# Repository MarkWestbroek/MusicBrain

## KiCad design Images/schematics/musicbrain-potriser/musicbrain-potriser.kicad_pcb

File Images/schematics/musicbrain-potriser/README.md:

# MusicBrain POT-RISER — MCP3208-riser voor het POT8-FRONT

**Status**: ERC 0, netlijst pad-voor-pad geverifieerd, DRC 0/0. Bord 28×80 mm, 2 lagen.
**Model**: route 2 — het domme POT8-FRONT ligt plat aan het paneel; deze smalle
riser staat eronder in het busboard-slot en draagt de elektronica.

## Connectoren

- **J1** (haakse male 2×10, onderrand): het busboard-slot in. Gebruikt alleen
  GND / +3V3 / SCLK / MOSI / MISO / CS; de rest (±12V, LDAC, IRQ, I2C, SPARE)
  is onaangesloten.
- **J2** (haakse male 1×10, bovenrand): het POT8-FRONT in.
  **Contract: 1 = GND, 2..9 = W1..W8 (lopers), 10 = +3V3.**
  ⚠️ Pin-1-oriëntatie t.o.v. de front-socket bij de eerste passing verifiëren
  (front-socket zit op de achterzijde); klopt de volgorde niet, dan de
  J2-map in `gen_potriser.py` spiegelen en regenereren.

## Elektrisch

- MCP3208 (SOIC-16), SPI mode 0, ratiometrisch (VREF = VDD = +3V3).
- CH0..CH7 = W1..W8 = paneel boven→onder.
- 100 nF-laadreservoir per loper (C1–C8) direct achter J2, 100 nF ontkoppeling (C9).
- Firmware: bestaande `MbPot8`-driver werkt ongewijzigd (zelfde chip + mapping).

## Waarom dit bord

De pot8-slotkaart (110×80, met haakse pots erop) is geen drager voor het
front-model: pots zitten in de weg, geen frontconnector en onnodig breed
(besluit 2026-07-11). Deze riser vervangt hem in het pot-spoor; de pot8-kaart
blijft bruikbaar als losstaand alternatief zonder front.

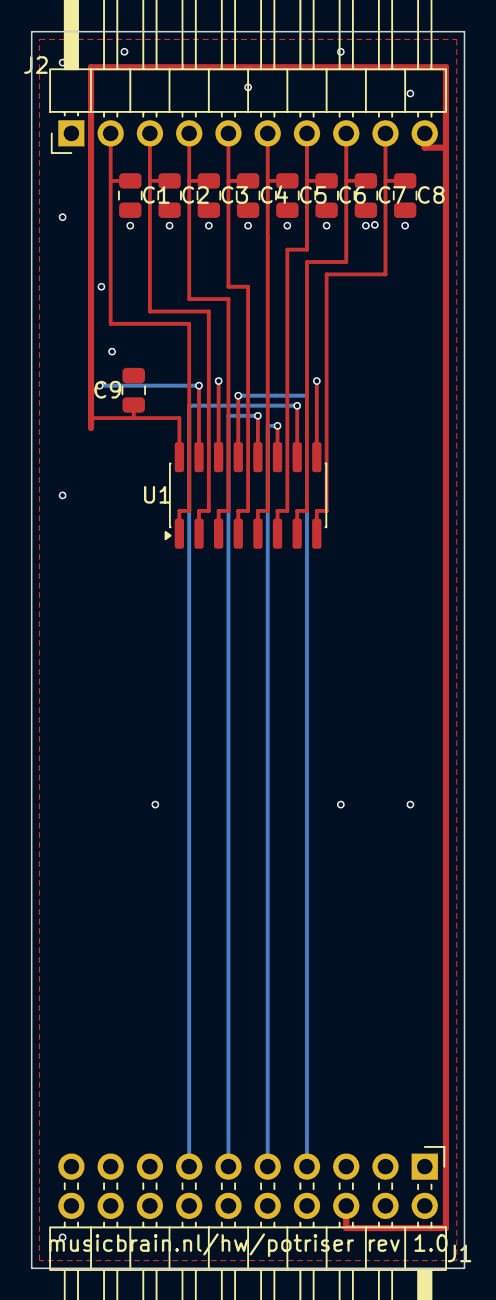
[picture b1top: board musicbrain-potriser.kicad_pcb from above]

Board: 2 copper layers, 28.0 x 80.0 mm, 12 parts (0 on the bottom side), 14 nets.

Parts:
C1, C2, C3, C4, C5, C6, C7, C8, C9: 100n; C_0805_2012Metric
J1: BUS; PinHeader_2x10_P2.54mm_Horizontal
J2: NAAR FRONT; PinHeader_1x10_P2.54mm_Horizontal
U1: MCP3208; SOIC-16_3.9x9.9mm_P1.27mm

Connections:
+3V3: C9.1, J1.6, J2.10, U1.15, U1.16
/CS: J1.13, U1.10
/MISO: J1.11, U1.12
/MOSI: J1.9, U1.11
/SCLK: J1.7, U1.13
/W1: C1.1, J2.2, U1.1
/W2: C2.1, J2.3, U1.2
/W3: C3.1, J2.4, U1.3
/W4: C4.1, J2.5, U1.4
/W5: C5.1, J2.6, U1.5
/W6: C6.1, J2.7, U1.6
/W7: C7.1, J2.8, U1.7
/W8: C8.1, J2.9, U1.8
GND: C1.2, C2.2, C3.2, C4.2, C5.2, C6.2, C7.2, C8.2, C9.2, J1.1, J1.3, J1.5, J1.8, J1.10, J1.12, J1.14, J2.1, U1.9, U1.14

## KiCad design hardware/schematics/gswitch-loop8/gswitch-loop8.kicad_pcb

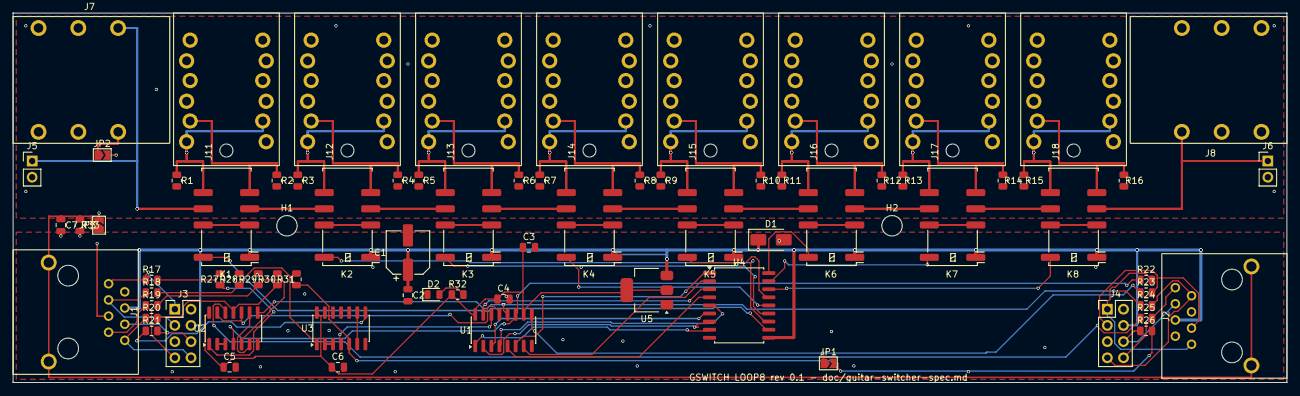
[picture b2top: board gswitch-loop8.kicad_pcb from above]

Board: 2 copper layers, 200.0 x 58.0 mm, 76 parts (0 on the bottom side), 82 nets.

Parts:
C1: 100u/25V; CP_Elec_6.3x7.7
C2, C4, C5, C6, C7: 100n; C_0805_2012Metric
C3: 10u; C_0805_2012Metric
D1: SMAJ15A; D_SMA
D2: LED-GN; LED_0805_2012Metric
H1, H2: M3; MH32
J1, J2: RJ45-S; RJ45_shielded
J3: CHAIN-LINK-IN; PinHeader_2x04_P2.54mm_Vertical
J4: CHAIN-LINK-UIT; PinHeader_2x04_P2.54mm_Vertical
J5: AUDIO-LINK-IN; PinHeader_1x02_P2.54mm_Vertical
J6: AUDIO-LINK-UIT; PinHeader_1x02_P2.54mm_Vertical
J7, J8: ACJS-MH; ACJS_MH
J11, J12, J13, J14, J15, J16, J17, J18: ACJS-MHD; ACJS_MHD
JP1: TERM; SolderJumper-2_P1.3mm_Open_TrianglePad1.0x1.5mm
JP2: IN-TN=AGND; SolderJumper-2_P1.3mm_Open_TrianglePad1.0x1.5mm
JP3: AGND=CHASSIS; SolderJumper-2_P1.3mm_Open_TrianglePad1.0x1.5mm
K1, K2, K3, K4, K5, K6, K7, K8: EE2-12NU/TQ2SA-12V; Relay_DPDT_Kemet_EE2_NU
R1, R2, R3, R4, R5, R6, R7, R8, R9, R10, R11, R12, R13, R14, R15, R16, R33: 1M; R_0805_2012Metric
R17, R18, R19, R20, R21, R22, R23, R24, R25, R26: 100R; R_0805_2012Metric
R27, R28, R29, R30, R31: 100k; R_0805_2012Metric
R32: 4k7; R_0805_2012Metric
U1: 74HC595; SOIC-16_3.9x9.9mm_P1.27mm
U2, U3: 74HC14; SOIC-14_3.9x8.7mm_P1.27mm
U4: ULN2803A; SOIC-18W_7.5x11.6mm_P1.27mm
U5: AMS1117-5.0; SOT-223-3_TabPin2

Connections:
+5V: C3.1, C4.1, C5.1, C6.1, R32.1, U1.10, U1.16, U2.14, U3.14, U5.2
+12V: C1.1, C2.1, D1.1, J1.4, J2.4, J3.4, J4.4, K1.1, K2.1, K3.1, K4.1, K5.1, K6.1, K7.1, K8.1, U4.10, U5.3
/AGND: J5.2, J6.2, J7.R, J7.RN, J7.S, J7.SN, J8.R, J8.RN, J8.S, J8.SN, J11.1, J11.2, J11.4, J11.5, J11.7, J11.8, J11.10, J11.11, J12.1, J12.2, J12.4, J12.5, J12.7, J12.8, J12.10, J12.11, J13.1, J13.2, J13.4, J13.5, J13.7, J13.8, J13.10, J13.11, J14.1, J14.2, J14.4, J14.5, J14.7, J14.8, J14.10, J14.11, J15.1, J15.2, J15.4, J15.5, J15.7, J15.8, J15.10, J15.11, J16.1, J16.2, J16.4, J16.5, J16.7, J16.8, J16.10, J16.11, J17.1, J17.2, J17.4, J17.5, J17.7, J17.8, J17.10, J17.11, J18.1, J18.2, J18.4, J18.5, J18.7, J18.8, J18.10, J18.11, JP2.2, JP3.2, R1.2, R2.2, R3.2, R4.2, R5.2, R6.2, R7.2, R8.2, R9.2, R10.2, R11.2, R12.2, R13.2, R14.2, R15.2, R16.2
/BYP1: K1.3, K1.10
/BYP2: K2.3, K2.10
/BYP3: K3.3, K3.10
/BYP4: K4.3, K4.10
/BYP5: K5.3, K5.10
/BYP6: K6.3, K6.10
/BYP7: K7.3, K7.10
/BYP8: K8.3, K8.10
/CHASSIS: C7.1, J1.SH, J2.SH, JP3.1, R33.1
/CLK_A: R17.2, R27.1, U2.1
/CLK_J: J1.1, J3.1, R17.1
/CLK_N: U2.2, U2.3
/CLK_O: R22.1, U1.11, U2.4
/CLK_T: J2.1, J4.1, R22.2
/D1: U1.1, U4.8
/D2: U1.2, U4.7
/D3: U1.3, U4.6
/D4: U1.4, U4.5
/D5: U1.5, U4.4
/D6: U1.6, U4.1
/D7: U1.7, U4.2
/D8: U1.15, U4.3
/DATA_A: R18.2, R28.1, U3.1
/DATA_J: J1.3, J3.3, R18.1
/DATA_N: U3.2, U3.3
/DATA_O: U1.14, U3.4
/DRETT_J: J2.6, J4.6, R26.1
/DRET_A: JP1.2, R26.2, R31.1, U3.5
/DRET_J: J1.6, J3.6, R21.2
/DRET_N: U3.6, U3.9
/DRET_O: R21.1, U3.8
/EN_A: R20.2, R30.1, U2.11
/EN_J: J1.8, J3.8, R20.1
/EN_O: R25.1, U2.12
/EN_T: J2.8, J4.8, R25.2
/INTN: J7.TN, JP2.1
/LATCH_A: R19.2, R29.1, U2.5
/LATCH_J: J1.7, J3.7, R19.1
/LATCH_N: U2.6, U2.9
/LATCH_O: R24.1, U1.12, U2.8
/LATCH_T: J2.7, J4.7, R24.2
/LEDA: D2.2, R32.2
/N0: J5.1, J7.T, K1.9
/N1: K1.4, K2.9
/N2: K2.4, K3.9
/N3: K3.4, K4.9
/N4: K4.4, K5.9
/N5: K5.4, K6.9
/N6: K6.4, K7.9
/N7: K7.4, K8.9
/N8: J6.1, J8.T, K8.4
/OE_N: U1.13, U2.10, U2.13
/RET1: J11.6, K1.5, R2.1
/RET2: J12.6, K2.5, R4.1
/RET3: J13.6, K3.5, R6.1
/RET4: J14.6, K4.5, R8.1
/RET5: J15.6, K5.5, R10.1
/RET6: J16.6, K6.5, R12.1
/RET7: J17.6, K7.5, R14.1
/RET8: J18.6, K8.5, R16.1
/RLY1: K1.12, U4.11
/RLY2: K2.12, U4.12
/RLY3: K3.12, U4.13
/RLY4: K4.12, U4.14
/RLY5: K5.12, U4.15
/RLY6: K6.12, U4.18
/RLY7: K7.12, U4.17
/RLY8: K8.12, U4.16
/SEND1: J11.3, J11.12, K1.8, R1.1
/SEND2: J12.3, J12.12, K2.8, R3.1
/SEND3: J13.3, J13.12, K3.8, R5.1
/SEND4: J14.3, J14.12, K4.8, R7.1
/SEND5: J15.3, J15.12, K5.8, R9.1
/SEND6: J16.3, J16.12, K6.8, R11.1
/SEND7: J17.3, J17.12, K7.8, R13.1
/SEND8: J18.3, J18.12, K8.8, R15.1
/SER: JP1.1, R23.1, U1.9
/SER_T: J2.3, J4.3, R23.2
GND: C1.2, C2.2, C3.2, C4.2, C5.2, C6.2, C7.2, D1.2, D2.1, J1.2, J1.5, J2.2, J2.5, J3.2, J3.5, J4.2, J4.5, R27.2, R28.2, R29.2, R30.2, R31.2, R33.2, U1.8, U2.7, U3.7, U3.11, U3.13, U4.9, U5.1

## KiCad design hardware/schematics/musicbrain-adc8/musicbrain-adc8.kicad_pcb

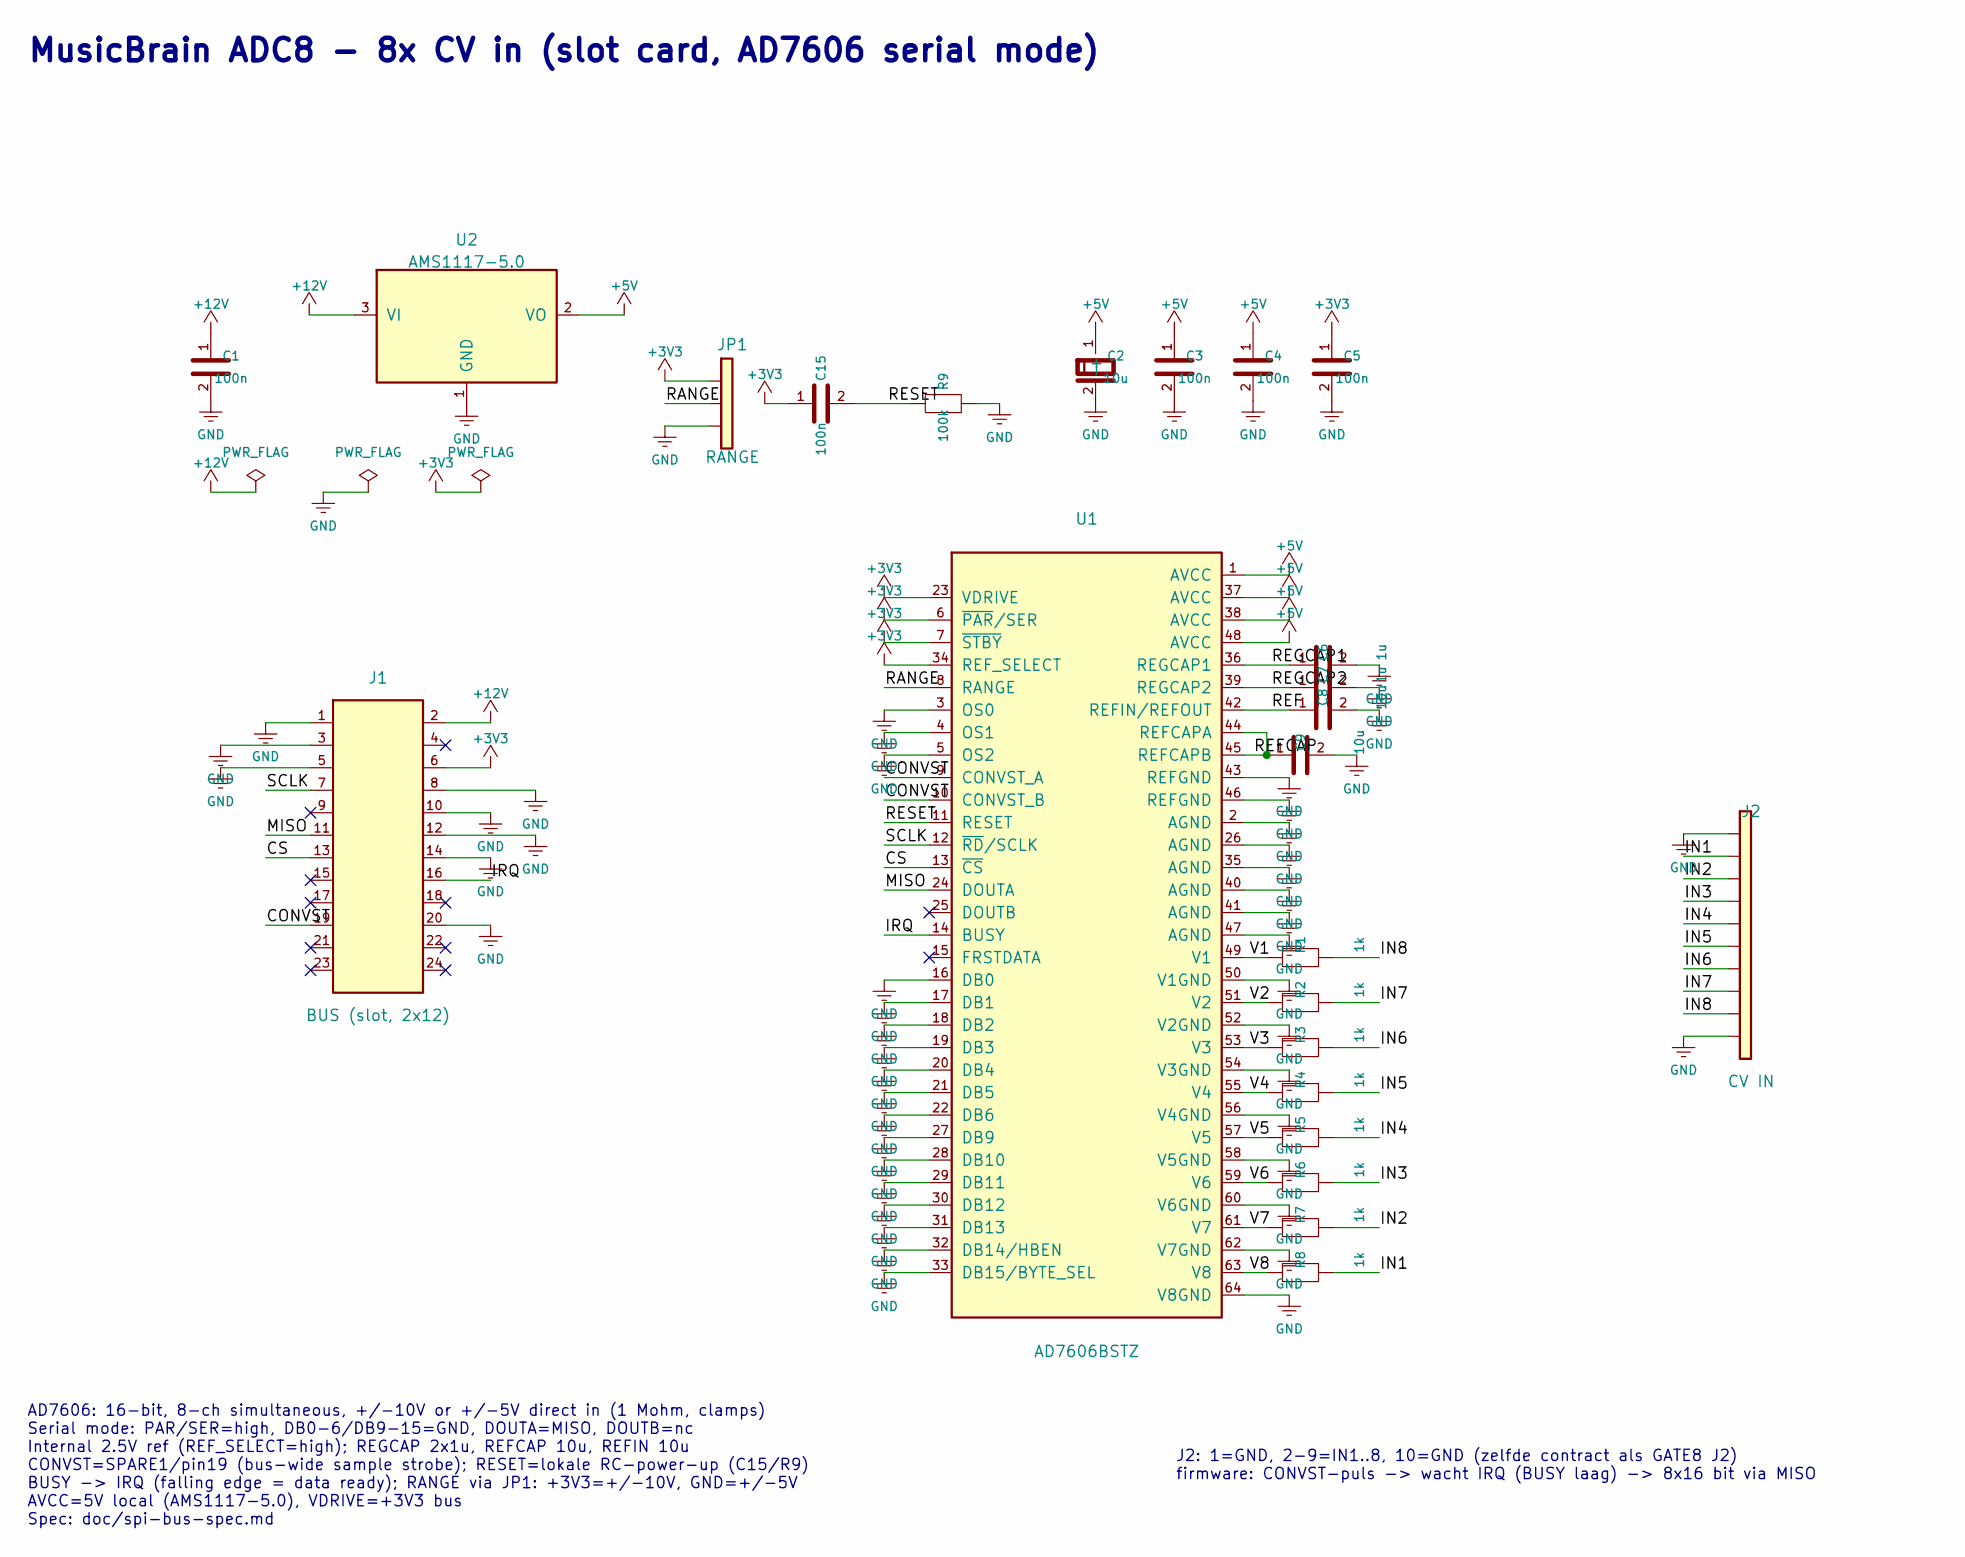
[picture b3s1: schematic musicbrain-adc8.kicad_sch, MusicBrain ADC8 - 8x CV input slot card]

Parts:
C1, C3, C4, C5, C15: 100n; C_0805_2012Metric
C2: 10u; CP_Elec_4x5.3
C6, C7: 1u; C_0805_2012Metric
C8, C9: 10u; C_0805_2012Metric
J1: BUS (slot, 2x12); PinHeader_2x12_P2.54mm_Horizontal
J2: CV IN; PinHeader_1x10_P2.54mm_Horizontal
JP1: RANGE; PinHeader_1x03_P2.54mm_Vertical
R1, R2, R3, R4, R5, R6, R7, R8: 1k; R_0805_2012Metric
R9: 100k; R_0805_2012Metric
U1: AD7606BSTZ; LQFP-64_10x10mm_P0.5mm
U2: AMS1117-5.0; SOT-223-3_TabPin2

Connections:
+3V3: C5.1, C15.1, J1.6, JP1.1, U1.6 (~PAR/SER), U1.7 (~STBY), U1.23 (VDRIVE), U1.34 (REF_SELECT)
+5V: C2.1 (+), C3.1, C4.1, U1.1 (AVCC), U1.37 (AVCC), U1.38 (AVCC), U1.48 (AVCC), U2.2 (VO)
+12V: C1.1, J1.2, U2.3 (VI)
/CONVST: J1.19, U1.9 (CONVST_A), U1.10 (CONVST_B)
/CS: J1.13, U1.13 (~CS)
/IN1: J2.2, R8.2
/IN2: J2.3, R7.2
/IN3: J2.4, R6.2
/IN4: J2.5, R5.2
/IN5: J2.6, R4.2
/IN6: J2.7, R3.2
/IN7: J2.8, R2.2
/IN8: J2.9, R1.2
/IRQ: J1.16, U1.14 (BUSY)
/MISO: J1.11, U1.24 (DOUTA)
/RANGE: JP1.2, U1.8 (RANGE)
/REF: C8.1, U1.42 (REFIN/REFOUT)
/REFCAP: C9.1, U1.44 (REFCAPA), U1.45 (REFCAPB)
/REGCAP1: C6.1, U1.36 (REGCAP1)
/REGCAP2: C7.1, U1.39 (REGCAP2)
/RESET: C15.2, R9.1, U1.11 (RESET)
/SCLK: J1.7, U1.12 (~RD/SCLK)
/V1: R1.1, U1.49 (V1)
/V2: R2.1, U1.51 (V2)
/V3: R3.1, U1.53 (V3)
/V4: R4.1, U1.55 (V4)
/V5: R5.1, U1.57 (V5)
/V6: R6.1, U1.59 (V6)
/V7: R7.1, U1.61 (V7)
/V8: R8.1, U1.63 (V8)
GND: C1.2, C2.2 (-), C3.2, C4.2, C5.2, C6.2, C7.2, C8.2, C9.2, J1.1, J1.3, J1.5, J1.8, J1.10, J1.12, J1.14, J1.20, J2.1, J2.10, JP1.3, R9.2, U1.2 (AGND), U1.3 (OS0), U1.4 (OS1), U1.5 (OS2), U1.16 (DB0), U1.17 (DB1), U1.18 (DB2), U1.19 (DB3), U1.20 (DB4), U1.21 (DB5), U1.22 (DB6), U1.26 (AGND), U1.27 (DB9), U1.28 (DB10), U1.29 (DB11), U1.30 (DB12), U1.31 (DB13), U1.32 (DB14/HBEN), U1.33 (DB15/BYTE_SEL), U1.35 (AGND), U1.40 (AGND), U1.41 (AGND), U1.43 (REFGND), U1.46 (REFGND), U1.47 (AGND), U1.50 (V1GND), U1.52 (V2GND), U1.54 (V3GND), U1.56 (V4GND), U1.58 (V5GND), U1.60 (V6GND), U1.62 (V7GND), U1.64 (V8GND), U2.1 (GND)

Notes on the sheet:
MusicBrain ADC8 - 8x CV in (slot card, AD7606 serial mode)
AD7606: 16-bit, 8-ch simultaneous, +/-10V or +/-5V direct in (1 Mohm, clamps) Serial mode: PAR/SER=high, DB0-6/DB9-15=GND, DOUTA=MISO, DOUTB=nc Internal 2.5V ref (REF_SELECT=high); REGCAP 2x1u, REFCAP 10u, REFIN 10u CONVST=SPARE1/pin19 (bus-wide sample strobe); RESET=lokale RC-power-up (C15/R9) BUS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
J2: 1=GND, 2-9=IN1..8, 10=GND (zelfde contract als GATE8 J2) firmware: CONVST-puls -> wacht IRQ (BUSY laag) -> 8x16 bit via MISO

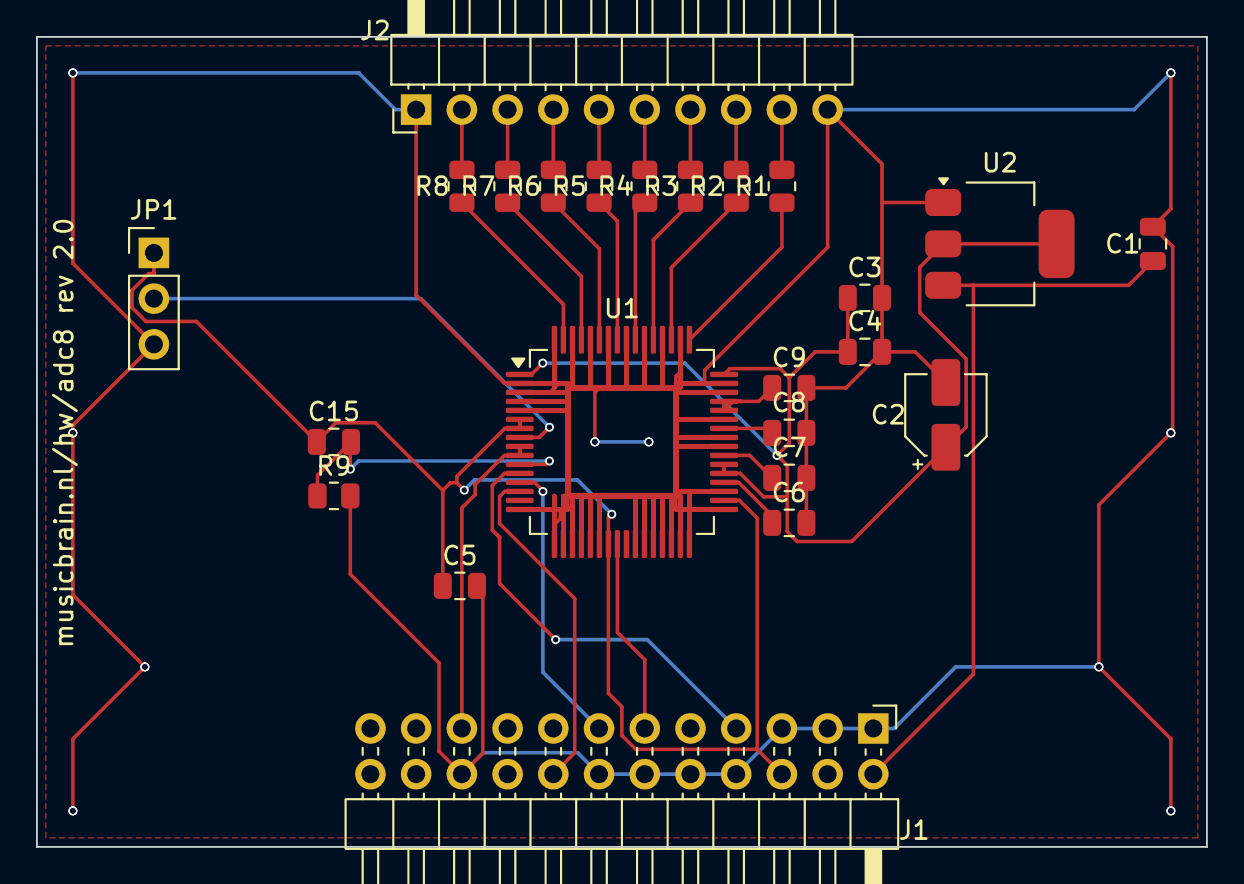
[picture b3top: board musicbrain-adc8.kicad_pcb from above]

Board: 2 copper layers, 65.0 x 45.0 mm, 24 parts (0 on the bottom side), 31 nets.

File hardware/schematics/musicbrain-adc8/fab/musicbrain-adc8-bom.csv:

"Comment","Designator","Footprint","LCSC Part #"
"100n","C1,C3,C4,C5","C_0805_2012Metric","C49678"
"10u","C2","CP_Elec_4x5.3","C3343"
"1u","C6,C7","C_0805_2012Metric","C5137478"
"10u","C8,C9","C_0805_2012Metric","C440198"
"BUS","J1","PinHeader_2x10_P2.54mm_Vertical",""
"CV IN","J2","PinHeader_1x10_P2.54mm_Vertical",""
"RANGE","JP1","PinHeader_1x03_P2.54mm_Vertical","C49257"
"1k","R1,R2,R3,R4,R5,R6,R7,R8","R_0805_2012Metric","C17513"
"100k","R9","R_0805_2012Metric","C149504"
"AD7606BSTZ","U1","LQFP-64_10x10mm_P0.5mm","C398827"
"AMS1117-5.0","U2","SOT-223-3_TabPin2","C6187"

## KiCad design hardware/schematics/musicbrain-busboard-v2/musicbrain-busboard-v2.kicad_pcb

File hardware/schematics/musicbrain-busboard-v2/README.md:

# MusicBrain busboard v2 — 16×CS / 12×IRQ + expansie + MIDI/CAN/codec/TUNE

**Status**: rev 2.0 AF — ERC 0, netlijst pad-voor-pad geverifieerd, **DRC 0/0**;
koper via de freerouting-pijplijn (+ hybride narun voor /CAN_TX en /IRQ5,
GND-hechtvia's automatisch geplaatst met `gnd_stitch.py`/`gnd_bridge.py`).
Fab-pakket in `fab/`. **Bestelbaar.**
**Plan + pintabel**: `doc/busboard-v2-plan.md` (leidend voor alle pinnummers).

## Audio over de bus (gen 2 / v3 — vooruitblik)

Vanaf busboard v3 dragen de slots ook de audio-lijnen (2×12, pinnen 21–24):
gedeelde klokrails + één datalijn per slot, verzameld op header J24 voor een
toekomstige FPGA-/TDM-mixer. Hoe dat samenhangt:

Details: `doc/busboard-v3-plan.md` + `doc/spi-bus-spec.md` v2.0.

## Blokken

- **Teensy 4.1** (west, verticaal, op 2× 1×24 socketstrip; SMD ≤ 6 mm mag
  eronder) — poort-daughterboard-model: de Teensy prikt op het busboard.
- **6 slots** (J1–J6, 2×10) + **2 hubs** (J7/J8, 2×5 IDC): zelfde slot/hub-
  pinout als v1 → alle bestaande kaarten passen ongewijzigd.
- **74HC154-CS-decoder** (U4): CSA0–3 + /E → 16 geografische CS-lijnen.
- **IRQ-keten**: 2× 74HC165 (U5 zuidwest: IRQ1–6; U6 noordoost: IRQ7–12,
  gelezen via decoder-Y14/IRQSTAT; per chip een PL-RC). Firmware-bytevolgorde
  1e byte = [IRQ5, IRQ6, x, x, IRQ1..4] — staat ook als noot in het schema.
- **Expansie**: 74LVC245-gebufferde lijnen + J21 (2×13 IDC) voor een tweede
  segment/busboard.
- **MIDI**: 2× IN (H11L1-opto's U9/U10) + 1× UIT (74LVC1G17 U11).
- **CAN3**: SN65HVD230 (U12) op Teensy-pins 30/31 + JP1-terminator + J16.
- **Codec-poort** (J17, 2×7): I2S1 (pins 7/8/20/21/23) + CODEC_RST (pin 22);
  I²C via de Qwiic-keten (J12).
- **TUNE-IN** (J18 + klem/deler, pin 1), **DLG-UART's** (J19/J20, Serial3/4).
- Voeding: J9 (2×5 IDC) → +12/−12 door; R-78E5.0 (U2) → 5 V; AMS1117 (U3)
  → 3V3; ontkoppelbank C1–C8.

## Mechanica-afwijkingen t.o.v. v1 (bovenplaat = v2!)

- M3 noord-midden: (115, 13) → **(163, 13)** (routecorridor).
- M3 zuid-west: (60, 122) → **(125, 122)** (lag midden op de DLG-headers).

## Werkwijze koper

Handrouting van vóór de placement-reparatie is geschrapt. De generator
(`hardware/kicad-generators/gen_bus2_pcb.py`) emit placement + GND-hechtvia's
en leest een freerouting-SES native in (zelfde pijplijn als enc5front:
DSN-export via de KiCad-MCP-server → GND-vlakken uit de DSN strippen → rand
0,6 mm inkrimpen → power-class 0,5 mm → Docker-freerouting, best-of-N →
netcheck + DRC als poortwachters).

## Aansluitoverzicht

### Pinouts

Bovenaanzicht van het bord (kijkend op de pinnen); pin 1 = vierkant. Gegenereerd uit het bordbestand met `hardware/kicad-generators/pinout_svg.py`.

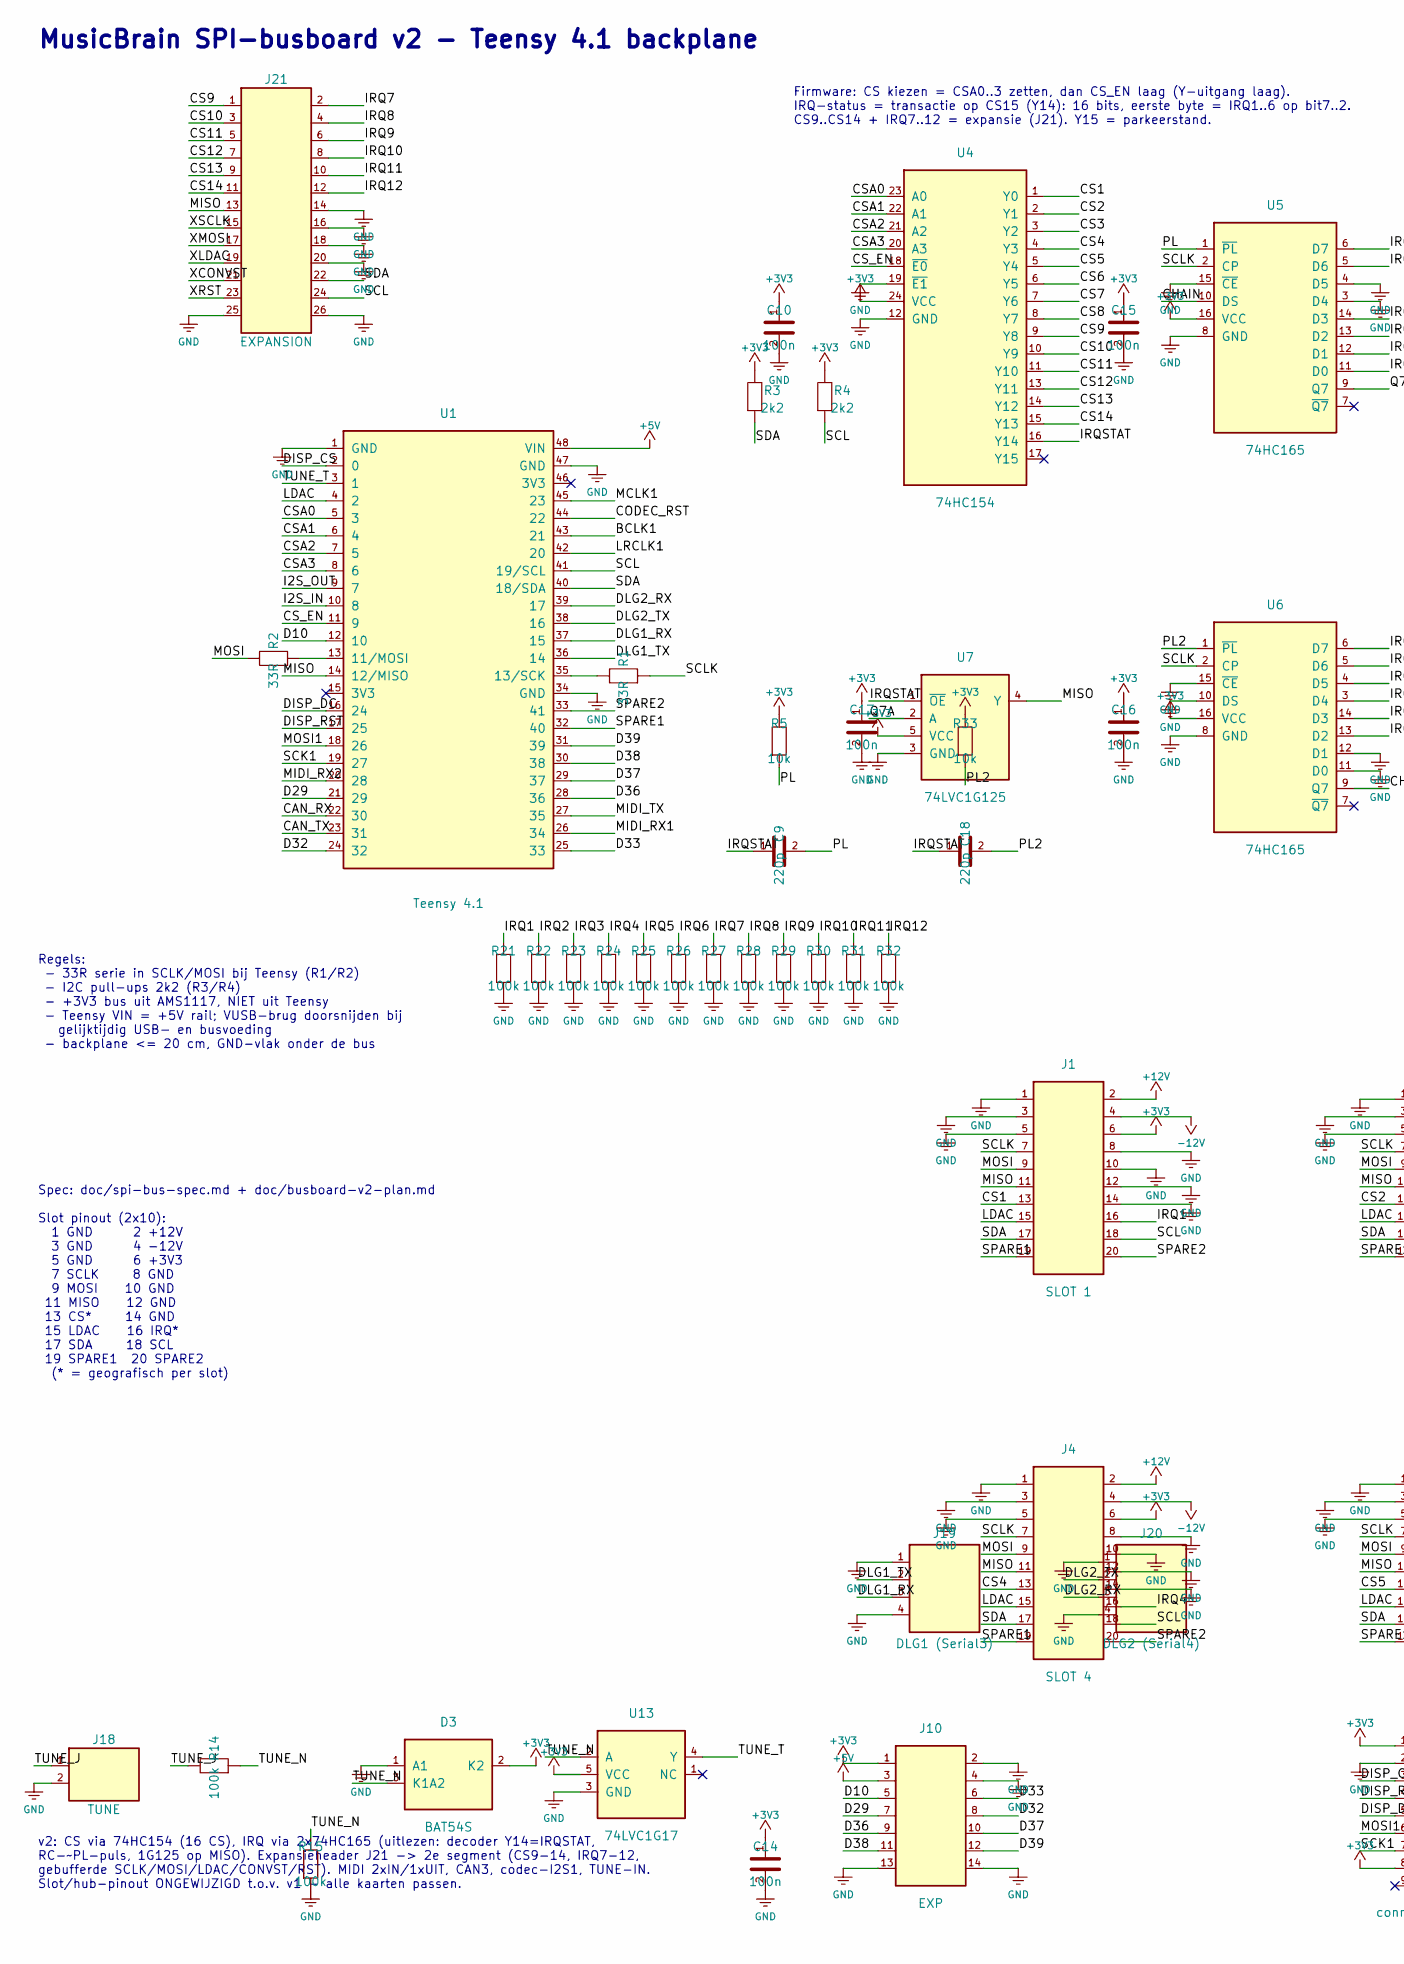
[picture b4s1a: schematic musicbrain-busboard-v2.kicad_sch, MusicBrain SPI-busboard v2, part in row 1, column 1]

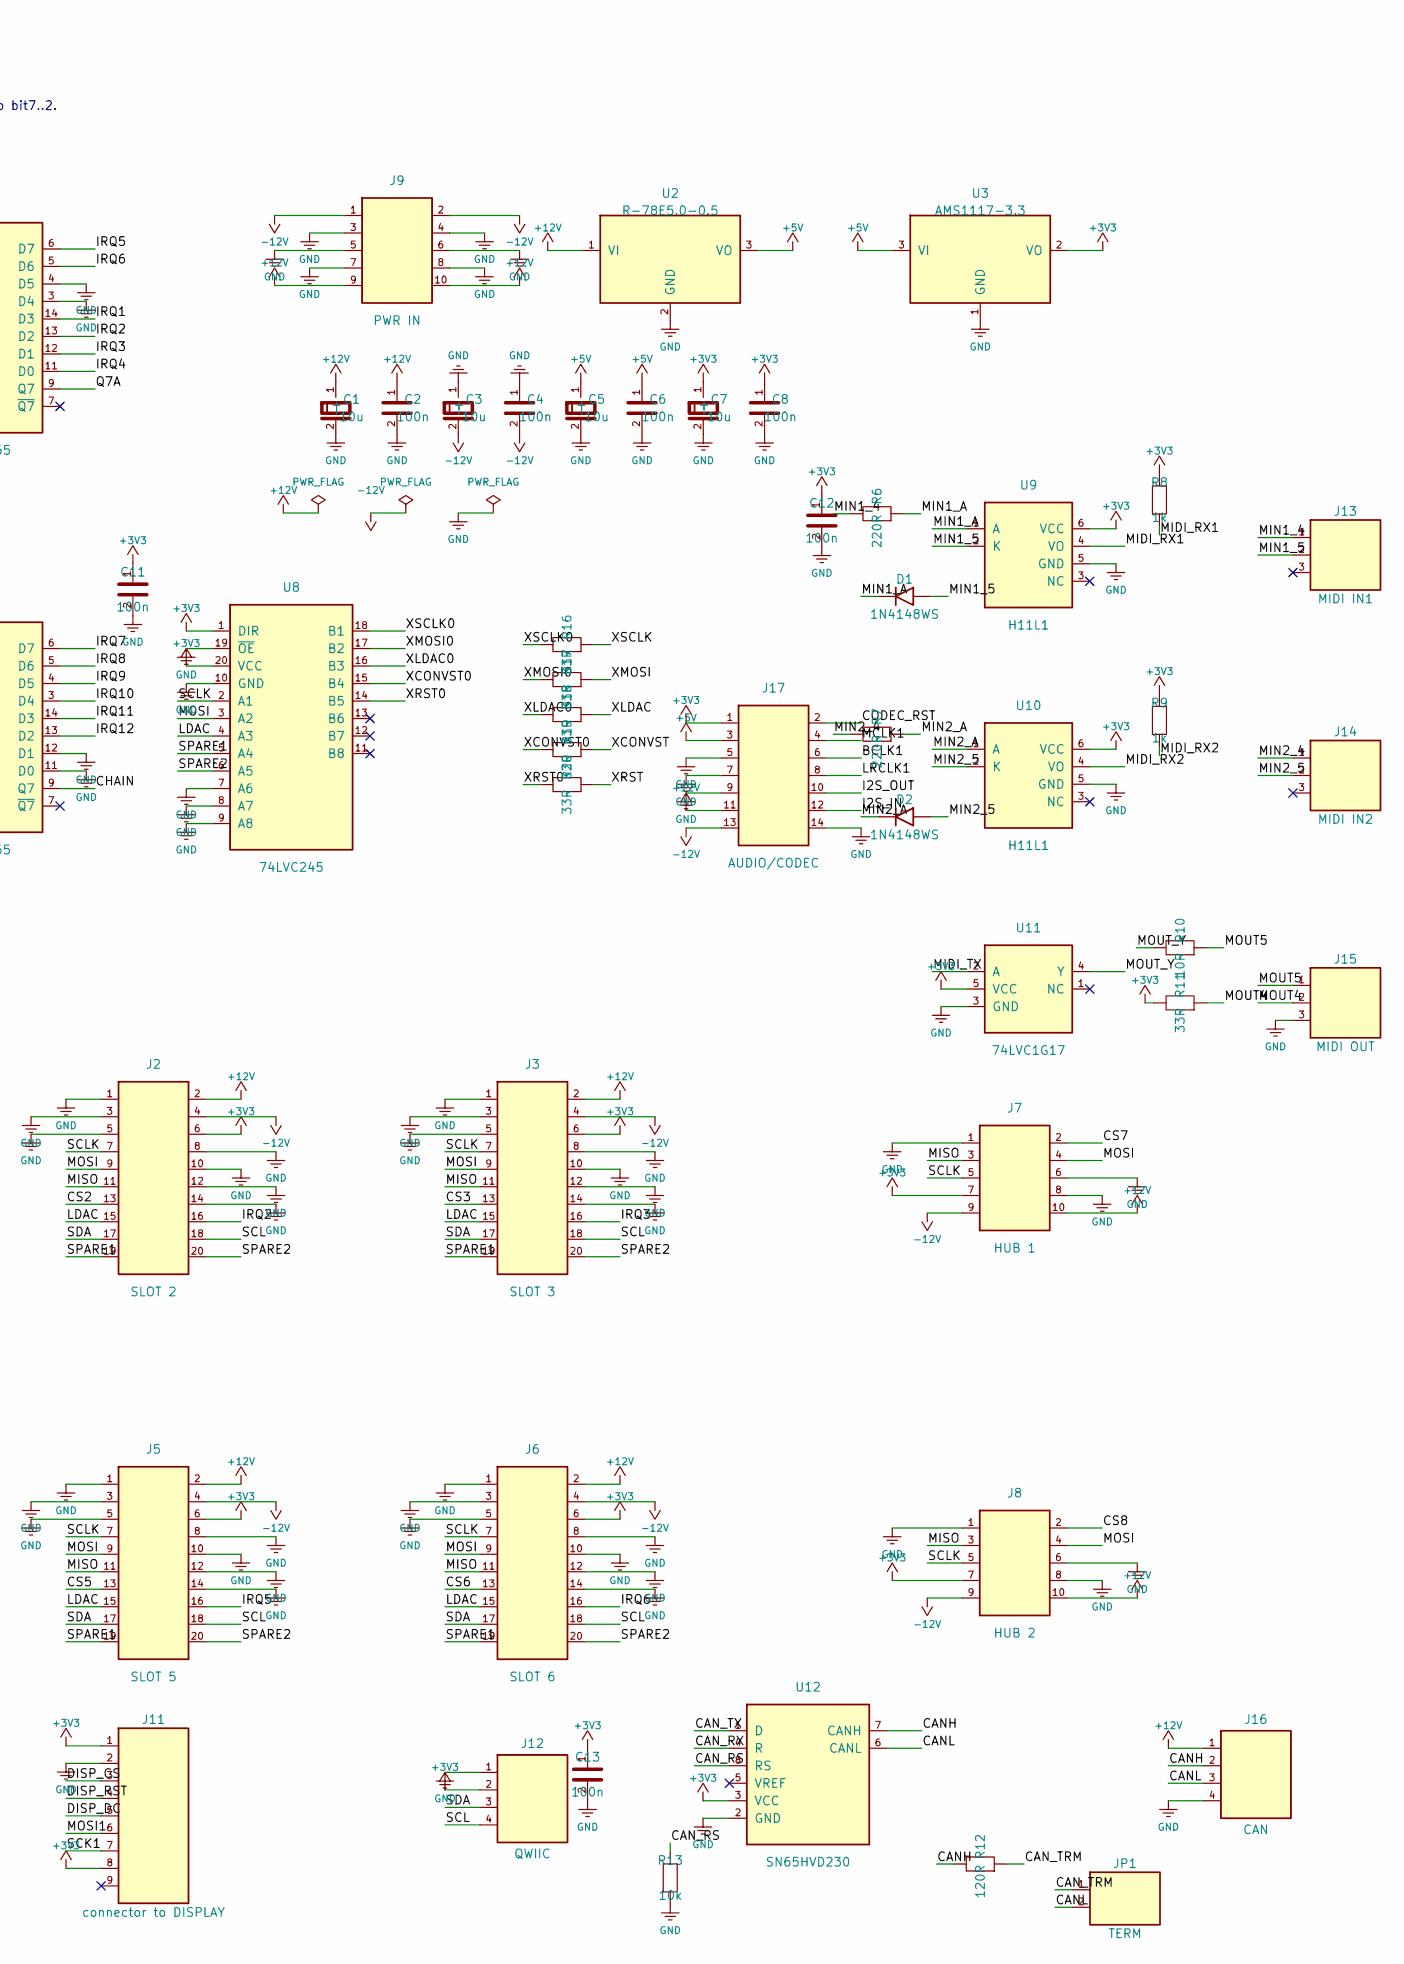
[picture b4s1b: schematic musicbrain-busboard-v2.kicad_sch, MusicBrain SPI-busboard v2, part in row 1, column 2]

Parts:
C1, C3, C5, C7: 10u; CP_Elec_4x5.3
C2, C4, C6, C8, C10, C11, C12, C13, C14, C15, C16, C17: 100n; C_0805_2012Metric
C9, C18: 220p; C_0805_2012Metric
D1, D2: 1N4148WS; D_SOD-323
D3: BAT54S; SOT-23
J1: SLOT 1; PinSocket_2x10_P2.54mm_Vertical
J2: SLOT 2; PinSocket_2x10_P2.54mm_Vertical
J3: SLOT 3; PinSocket_2x10_P2.54mm_Vertical
J4: SLOT 4; PinSocket_2x10_P2.54mm_Vertical
J5: SLOT 5; PinSocket_2x10_P2.54mm_Vertical
J6: SLOT 6; PinSocket_2x10_P2.54mm_Vertical
J7: HUB 1; IDC-Header_2x05_P2.54mm_Vertical
J8: HUB 2; IDC-Header_2x05_P2.54mm_Vertical
J9: PWR IN; IDC-Header_2x05_P2.54mm_Vertical
J10: EXP; PinHeader_2x07_P2.54mm_Vertical
J11: connector to DISPLAY; PinHeader_1x09_P2.54mm_Vertical
J12: QWIIC; PinHeader_1x04_P2.54mm_Vertical
J13: MIDI IN1; PinHeader_1x03_P2.54mm_Vertical
J14: MIDI IN2; PinHeader_1x03_P2.54mm_Vertical
J15: MIDI OUT; PinHeader_1x03_P2.54mm_Vertical
J16: CAN; PinHeader_1x04_P2.54mm_Vertical
J17: AUDIO/CODEC; PinHeader_2x07_P2.54mm_Vertical
J18: TUNE; PinHeader_1x02_P2.54mm_Vertical
J19: DLG1 (Serial3); PinHeader_1x04_P2.54mm_Vertical
J20: DLG2 (Serial4); PinHeader_1x04_P2.54mm_Vertical
J21: EXPANSION; IDC-Header_2x13_P2.54mm_Vertical
JP1: TERM; SolderJumper-2_P1.3mm_Open_TrianglePad1.0x1.5mm
R1, R2, R11, R16, R17, R18, R19, R20: 33R; R_0805_2012Metric
R3, R4: 2k2; R_0805_2012Metric
R5, R13, R33: 10k; R_0805_2012Metric
R6, R7: 220R; R_0805_2012Metric
R8, R9: 1k; R_0805_2012Metric
R10: 10R; R_0805_2012Metric
R12: 120R; R_0805_2012Metric
R14, R15, R21, R22, R23, R24, R25, R26, R27, R28, R29, R30, R31, R32: 100k; R_0805_2012Metric
U1: Teensy 4.1
U2: R-78E5.0-0.5; Converter_DCDC_RECOM_R-78E-0.5_THT
U3: AMS1117-3.3; SOT-223-3_TabPin2
U4: 74HC154; SOIC-24W_7.5x15.4mm_P1.27mm
U5, U6: 74HC165; SOIC-16_3.9x9.9mm_P1.27mm
U7: 74LVC1G125; SOT-23-5
U8: 74LVC245; SOIC-20W_7.5x12.8mm_P1.27mm
U9, U10: H11L1; DIP-6_W7.62mm
U11, U13: 74LVC1G17; SOT-23-5
U12: SN65HVD230; SOIC-8_3.9x4.9mm_P1.27mm

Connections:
+3V3: C7.1 (+), C8.1, C10.1, C11.1, C12.1, C13.1, C14.1, C15.1, C16.1, C17.1, D3.2 (K2), J1.6, J2.6, J3.6, J4.6, J5.6, J6.6, J7.7, J8.7, J10.1, J11.1, J11.8, J12.2, J17.1, R3.1, R4.1, R5.1, R8.1, R9.1, R11.1, R33.1, U3.2 (VO), U4.24 (VCC), U5.16 (VCC), U6.16 (VCC), U7.5 (VCC), U8.1 (DIR), U8.20 (VCC), U9.6 (VCC), U10.6 (VCC), U11.5 (VCC), U12.3 (VCC), U13.5 (VCC)
+5V: C5.1 (+), C6.1, J10.3, J17.3, U1.48 (VIN), U2.3 (VO), U3.3 (VI)
+12V: C1.1 (+), C2.1, J1.2, J2.2, J3.2, J4.2, J5.2, J6.2, J7.10, J8.10, J9.9, J9.10, J16.1, J17.11, U2.1 (VI)
-12V: C3.2 (-), C4.2, J1.4, J2.4, J3.4, J4.4, J5.4, J6.4, J7.9, J8.9, J9.1, J9.2, J17.13
/BCLK1: J17.6, U1.43 (21)
/CANH: J16.2, R12.1, U12.7 (CANH)
/CANL: J16.3, JP1.2, U12.6 (CANL)
/CAN_RS: R13.1, U12.8 (RS)
/CAN_RX: U1.22 (30), U12.4 (R)
/CAN_TRM: JP1.1, R12.2
/CAN_TX: U1.23 (31), U12.1 (D)
/CHAIN: U5.10 (DS), U6.9 (Q7)
/CODEC_RST: J17.2, U1.44 (22)
/CS1: J1.13, U4.1 (Y0)
/CS2: J2.13, U4.2 (Y1)
/CS3: J3.13, U4.3 (Y2)
/CS4: J4.13, U4.4 (Y3)
/CS5: J5.13, U4.5 (Y4)
/CS6: J6.13, U4.6 (Y5)
/CS7: J7.2, U4.7 (Y6)
/CS8: J8.2, U4.8 (Y7)
/CS9: J21.1, U4.9 (Y8)
/CS10: J21.3, U4.10 (Y9)
/CS11: J21.5, U4.11 (Y10)
/CS12: J21.7, U4.13 (Y11)
/CS13: J21.9, U4.14 (Y12)
/CS14: J21.11, U4.15 (Y13)
/CSA0: U1.5 (3), U4.23 (A0)
/CSA1: U1.6 (4), U4.22 (A1)
/CSA2: U1.7 (5), U4.21 (A2)
/CSA3: U1.8 (6), U4.20 (A3)
/CS_EN: U1.11 (9), U4.18 (~E0)
/D10: J10.5, U1.12 (10)
/D29: J10.7, U1.21 (29)
/D32: J10.8, U1.24 (32)
/D33: J10.6, U1.25 (33)
/D36: J10.9, U1.28 (36)
/D37: J10.10, U1.29 (37)
/D38: J10.11, U1.30 (38)
/D39: J10.12, U1.31 (39)
/DISP_CS: J11.3, U1.2 (0)
/DISP_DC: J11.5, U1.16 (24)
/DISP_RST: J11.4, U1.17 (25)
/DLG1_RX: J19.3, U1.37 (15)
/DLG1_TX: J19.2, U1.36 (14)
/DLG2_RX: J20.3, U1.39 (17)
/DLG2_TX: J20.2, U1.38 (16)
/I2S_IN: J17.12, U1.10 (8)
/I2S_OUT: J17.10, U1.9 (7)
/IRQ1: J1.16, R21.1, U5.14 (D3)
/IRQ2: J2.16, R22.1, U5.13 (D2)
/IRQ3: J3.16, R23.1, U5.12 (D1)
/IRQ4: J4.16, R24.1, U5.11 (D0)
/IRQ5: J5.16, R25.1, U5.6 (D7)
/IRQ6: J6.16, R26.1, U5.5 (D6)
/IRQ7: J21.2, R27.1, U6.6 (D7)
/IRQ8: J21.4, R28.1, U6.5 (D6)
/IRQ9: J21.6, R29.1, U6.4 (D5)
/IRQ10: J21.8, R30.1, U6.3 (D4)
/IRQ11: J21.10, R31.1, U6.14 (D3)
/IRQ12: J21.12, R32.1, U6.13 (D2)
/IRQSTAT: C9.1, C18.1, U4.16 (Y14), U7.1 (~OE)
/LDAC: J1.15, J2.15, J3.15, J4.15, J5.15, J6.15, U1.4 (2), U8.4 (A3)
/LRCLK1: J17.8, U1.42 (20)
/MCLK1: J17.4, U1.45 (23)
/MIDI_RX1: R8.2, U1.26 (34), U9.4 (VO)
/MIDI_RX2: R9.2, U1.20 (28), U10.4 (VO)
/MIDI_TX: U1.27 (35), U11.2 (A)
/MIN1_4: J13.1, R6.1
/MIN1_5: D1.2 (A), J13.2, U9.2 (K)
/MIN1_A: D1.1 (K), R6.2, U9.1 (A)
/MIN2_4: J14.1, R7.1
/MIN2_5: D2.2 (A), J14.2, U10.2 (K)
/MIN2_A: D2.1 (K), R7.2, U10.1 (A)
/MISO: J1.11, J2.11, J3.11, J4.11, J5.11, J6.11, J7.3, J8.3, J21.13, U1.14 (12/MISO), U7.4 (Y)
/MOSI: J1.9, J2.9, J3.9, J4.9, J5.9, J6.9, J7.4, J8.4, R2.1, U8.3 (A2)
/MOSI1: J11.6, U1.18 (26)
/MOUT4: J15.2, R11.2
/MOUT5: J15.1, R10.2
/MOUT_Y: R10.1, U11.4 (Y)
/PL: C9.2, R5.2, U5.1 (~PL)
/PL2: C18.2, R33.2, U6.1 (~PL)
/Q7A: U5.9 (Q7), U7.2 (A)
/SCK1: J11.7, U1.19 (27)
/SCL: J1.18, J2.18, J3.18, J4.18, J5.18, J6.18, J12.4, J21.24, R4.2, U1.41 (19/SCL)
/SCLK: J1.7, J2.7, J3.7, J4.7, J5.7, J6.7, J7.5, J8.5, R1.2, U5.2 (CP), U6.2 (CP), U8.2 (A1)
/SDA: J1.17, J2.17, J3.17, J4.17, J5.17, J6.17, J12.3, J21.22, R3.2, U1.40 (18/SDA)
/SPARE1: J1.19, J2.19, J3.19, J4.19, J5.19, J6.19, U1.32 (40), U8.5 (A4)
/SPARE2: J1.20, J2.20, J3.20, J4.20, J5.20, J6.20, U1.33 (41), U8.6 (A5)
/TUNE_J: J18.1, R14.1
/TUNE_N: D3.3 (K1A2), R14.2, R15.1, U13.2 (A)
/TUNE_T: U1.3 (1), U13.4 (Y)
/XCONVST: J21.21, R19.2
/XCONVST0: R19.1, U8.15 (B4)
/XLDAC: J21.19, R18.2
/XLDAC0: R18.1, U8.16 (B3)
/XMOSI: J21.17, R17.2
/XMOSI0: R17.1, U8.17 (B2)
/XRST: J21.23, R20.2
/XRST0: R20.1, U8.14 (B5)
/XSCLK: J21.15, R16.2
/XSCLK0: R16.1, U8.18 (B1)
GND: C1.2 (-), C2.2, C3.1 (+), C4.1, C5.2 (-), C6.2, C7.2 (-), C8.2, C10.2, C11.2, C12.2, C13.2, C14.2, C15.2, C16.2, C17.2, D3.1 (A1), J1.1, J1.3, J1.5, J1.8, J1.10, J1.12, J1.14, J2.1, J2.3, J2.5, J2.8, J2.10, J2.12, J2.14, J3.1, J3.3, J3.5, J3.8, J3.10, J3.12, J3.14, J4.1, J4.3, J4.5, J4.8, J4.10, J4.12, J4.14, J5.1, J5.3, J5.5, J5.8, J5.10, J5.12, J5.14, J6.1, J6.3, J6.5, J6.8, J6.10, J6.12, J6.14, J7.1, J7.6, J7.8, J8.1, J8.6, J8.8, J9.3, J9.4, J9.5, J9.6, J9.7, J9.8, J10.2, J10.4, J10.13, J10.14, J11.2, J12.1, J15.3, J16.4, J17.5, J17.7, J17.9, J17.14, J18.2, J19.1, J19.4, J20.1, J20.4, J21.14, J21.16, J21.18, J21.20, J21.25, J21.26, R13.2, R15.2, R21.2, R22.2, R23.2, R24.2, R25.2, R26.2, R27.2, R28.2, R29.2, R30.2, R31.2, R32.2, U1.1 (GND), U1.34 (GND), U1.47 (GND), U2.2 (GND), U3.1 (GND), U4.12 (GND), U4.19 (~E1), U5.3 (D4), U5.4 (D5), U5.8 (GND), U5.15 (~CE), U6.8 (GND), U6.10 (DS), U6.11 (D0), U6.12 (D1), U6.15 (~CE), U7.3 (GND), U8.7 (A6), U8.8 (A7), U8.9 (A8), U8.10 (GND), U8.19 (~OE), U9.5 (GND), U10.5 (GND), U11.3 (GND), U12.2 (GND), U13.3 (GND)
unnamed: R2.2, U1.13 (11/MOSI)
unnamed: R1.1, U1.35 (13/SCK)

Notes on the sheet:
MusicBrain SPI-busboard v2 - Teensy 4.1 backplane
v2: CS via 74HC154 (16 CS), IRQ via 2x74HC165 (uitlezen: decoder Y14=IRQSTAT, RC-~PL-puls, 1G125 op MISO). Expansieheader J21 -> 2e segment (CS9-14, IRQ7-12, gebufferde SCLK/MOSI/LDAC/CONVST/RST). MIDI 2xIN/1xUIT, CAN3, codec-I2S1, TUNE-IN. Slot/hub-pinout ONGEWIJZIGD t.o.v. v1 - alle kaarten passe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
Spec: doc/spi-bus-spec.md + doc/busboard-v2-plan.md Slot pinout (2x10): 1 GND 2 +12V 3 GND 4 -12V 5 GND 6 +3V3 7 SCLK 8 GND 9 MOSI 10 GND 11 MISO 12 GND 13 CS* 14 GND 15 LDAC 16 IRQ* 17 SDA 18 SCL 19 SPARE1 20 SPARE2 (* = geografisch per slot)
Regels: - 33R serie in SCLK/MOSI bij Teensy (R1/R2) - I2C pull-ups 2k2 (R3/R4) - +3V3 bus uit AMS1117, NIET uit Teensy - Teensy VIN = +5V rail; VUSB-brug doorsnijden bij gelijktijdig USB- en busvoeding - backplane <= 20 cm, GND-vlak onder de bus
Firmware: CS kiezen = CSA0..3 zetten, dan CS_EN laag (Y-uitgang laag). IRQ-status = transactie op CS15 (Y14): 16 bits, eerste byte = IRQ1..6 op bit7..2. CS9..CS14 + IRQ7..12 = expansie (J21). Y15 = parkeerstand.
